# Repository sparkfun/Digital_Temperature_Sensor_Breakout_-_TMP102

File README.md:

Digital Temperature Sensor Breakout - TMP102
============================================

[*Digital Temperature Sensor Breakout - TMP102 (SEN-11931)*](https://www.sparkfun.com/products/11931)

Breakout board for TMP102 digital temperature sensor. [The datasheet can be found here.](https://www.sparkfun.com/datasheets/Sensors/Temperature/tmp102.pdf)

This board was created in Eagle v6.4.0. 

Repository Contents
-------------------

* **/Hardware** - All Eagle design files (.brd and .sch)
* **/Production** - Production panel files

Documentation
-------------------

* [Arduino Library](https://github.com/sparkfun/SparkFun_TMP102_Arduino_Library)
* [Hookup Guide](https://learn.sparkfun.com/tutorials/tmp102-digital-temperature-sensor-hookup-guide)

License Information
-------------------
The hardware is released under [Creative Commons Share-alike 3.0](http://creativecommons.org/licenses/by-sa/3.0/).  
All other code is open source so please feel free to do anything you want with it; you buy me a beer if you use this and we meet someday ([Beerware license](http://en.wikipedia.org/wiki/Beerware)).

Design by Kade Alexander Jensen

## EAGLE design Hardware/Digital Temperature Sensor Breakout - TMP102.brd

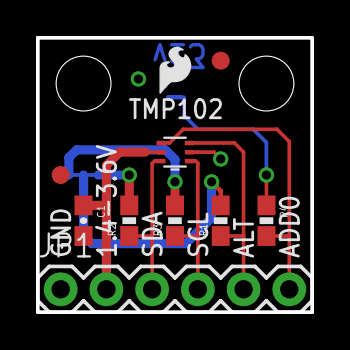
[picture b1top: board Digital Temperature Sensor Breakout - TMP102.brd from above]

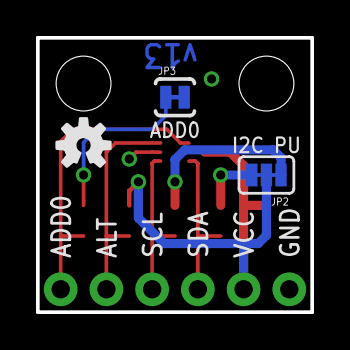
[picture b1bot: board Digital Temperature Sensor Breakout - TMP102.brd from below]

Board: 2 copper layers, 15.2 x 15.2 mm, 17 parts (3 on the bottom side), 9 nets.

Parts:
C1: 0.1uF; 0603-CAP
FRAME2: FRAME-LETTER; CREATIVE_COMMONS
JP1: 1X06
JP2: PAD-JUMPER-3-3OF3_NC_BY_TRACE_YES_SILK_FULL_BOX
JP3: ADD0; PAD-JUMPER-2-NC_BY_TRACE_YES_SILK
JP5, JP6: FIDUCIAL1X2; FIDUCIAL-1X2
JP7, JP8: STAND-OFFTIGHT; STAND-OFF-TIGHT
LOGO2: SFE_LOGO_FLAME.1_INCH; SFE_LOGO_FLAME_.1
LOGO3: OSHW-LOGOS; OSHW-LOGO-S
R1, R4: 10K; 0603-RES
R2, R3: 4.7K; 0603-RES
U1: TMP1021:1; SOT563-2
U$2: REVISION

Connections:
ADD0: JP1.6, R4.2, U1.4
ALERT: JP1.5, R1.1, U1.3
GND: C1.2, JP1.1, JP3.2, U1.2
unnamed: JP2.1, R3.2
unnamed: JP2.3, R2.2
unnamed: JP3.1, R4.1
SCL: JP1.4, R3.1, U1.1
SDA: JP1.3, R2.1, U1.6
VCC: C1.1, JP1.2, JP2.2, R1.2, U1.5

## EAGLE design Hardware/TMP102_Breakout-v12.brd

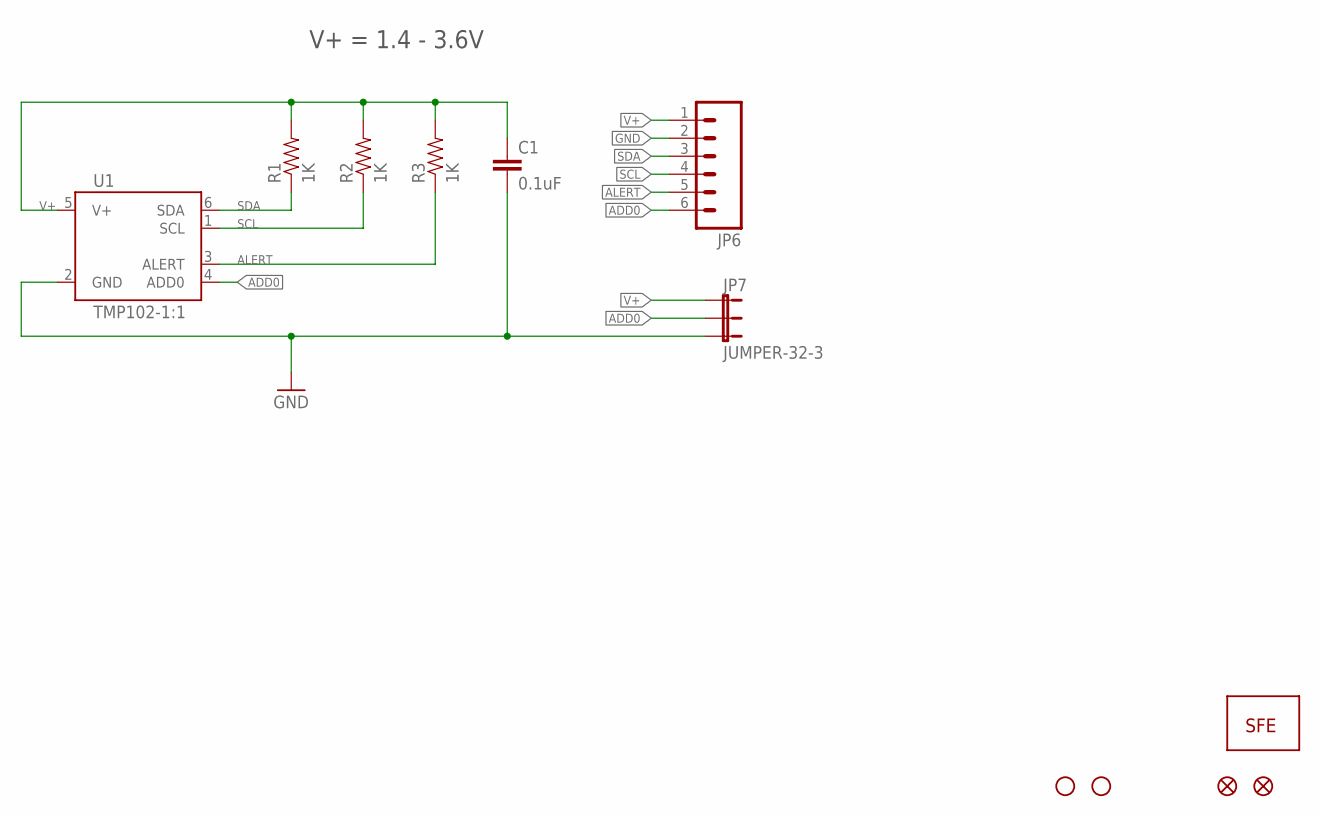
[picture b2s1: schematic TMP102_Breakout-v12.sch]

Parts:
C1: 0.1uF; 0603-CAP
JP1, JP2: STAND-OFFTIGHT; STAND-OFF-TIGHT
JP3: LOGO-SFESK; SFE-LOGO-FLAME
JP4, JP5: FIDUCIAL1X2; FIDUCIAL-1X2
JP6: M06SIP; 1X06
JP7: JUMPER-32-3; SJ_3_PASTE2&3
R1, R2, R3: 1K; 0603-RES
U1: TMP102-1:1; SOT563-2

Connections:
ADD0: JP6.6, JP7.2, U1.4 (ADD0)
ALERT: JP6.5, R3.1, U1.3 (ALERT)
GND: C1.2, JP6.2, JP7.3, U1.2 (GND)
SCL: JP6.4, R2.1, U1.1 (SCL)
SDA: JP6.3, R1.1, U1.6 (SDA)
V+: C1.1, JP6.1, JP7.1, R1.2, R2.2, R3.2, U1.5 (V+)

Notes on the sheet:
V+ = 1.4 - 3.6V

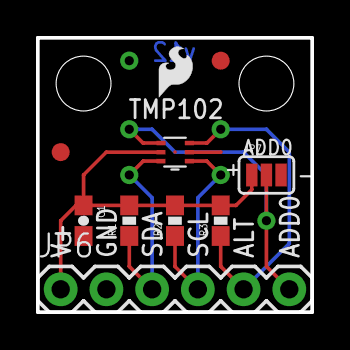
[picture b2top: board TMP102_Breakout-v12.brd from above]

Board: 2 copper layers, 15.2 x 15.2 mm, 13 parts (1 on the bottom side), 6 nets.

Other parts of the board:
U$1: OSHW-LOGO-S

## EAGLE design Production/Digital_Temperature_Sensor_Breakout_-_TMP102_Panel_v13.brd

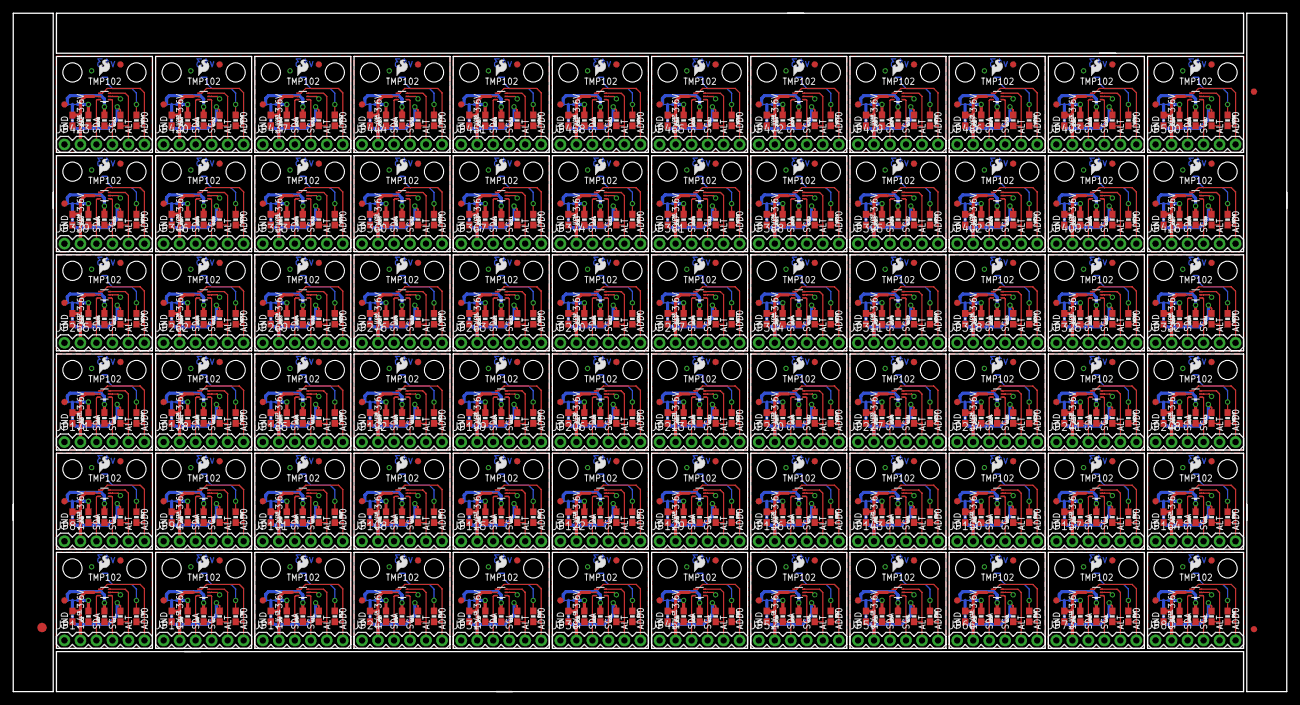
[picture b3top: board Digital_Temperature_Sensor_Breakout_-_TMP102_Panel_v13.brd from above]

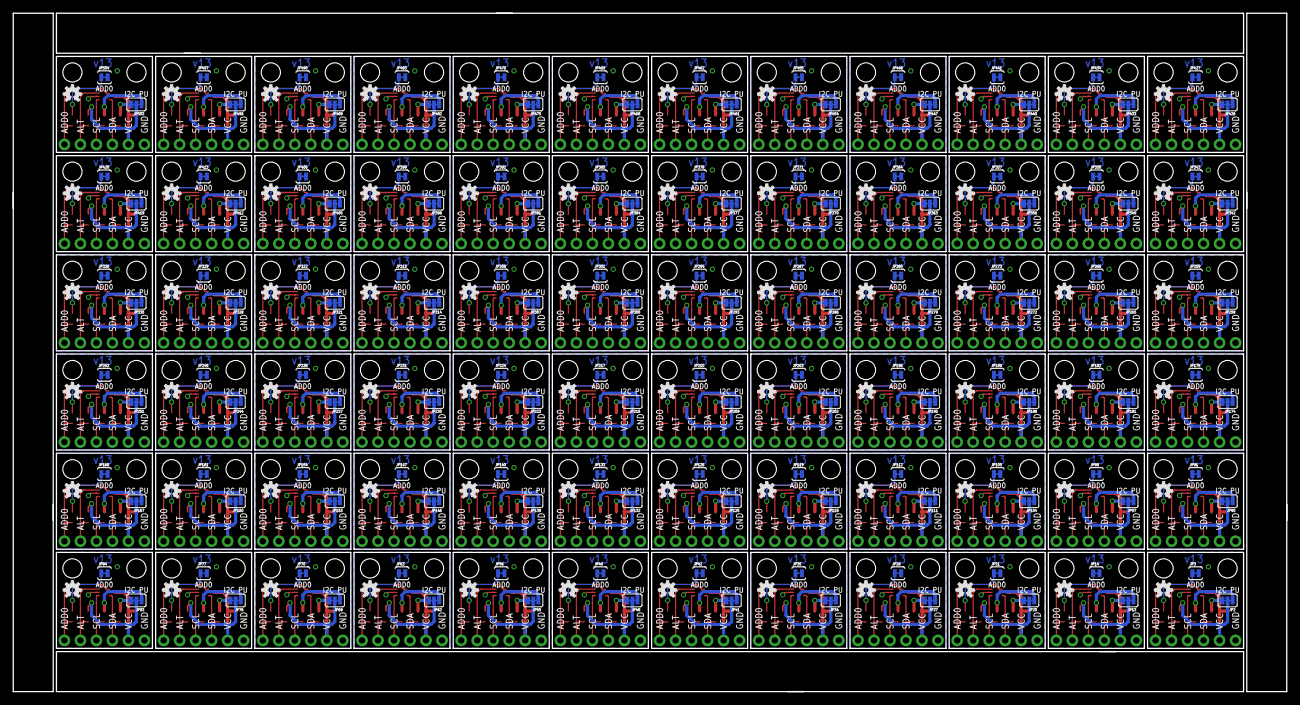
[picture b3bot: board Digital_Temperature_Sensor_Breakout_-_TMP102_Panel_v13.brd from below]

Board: 2 copper layers, 202.2 x 107.7 mm, 1083 parts (216 on the bottom side), 648 nets.

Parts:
C1, C2, C3, C4, C5, C6, C7, C8, C9, C10, C11, C12, C13, C14, C15, C16, C17, C18, C19, C20, C21, C22, C23, C24, C25, C26, C27, C28, C29, C30, C31, C32, C33, C34, C35, C36, C37, C38, C39, C40, C41, C42, C43, C44, C45, C46, C47, C48, C49, C50, C51, C52, C53, C54, C55, C56, C57, C58, C59, C60, C61, C62, C63, C64, C65, C66, C67, C68, C69, C70, C71, C72: 0.1uF; 0603-CAP
E$1: FIDUCIAL-1.5X3
E$2, E$5: FIDUCIAL-1X2
JP1, JP10, JP17, JP24, JP31, JP38, JP45, JP52, JP59, JP66, JP73, JP80, JP87, JP94, JP101, JP108, JP115, JP122, JP129, JP136, JP143, JP150, JP157, JP164, JP171, JP178, JP185, JP192, JP199, JP206, JP213, JP220, JP227, JP234, JP241, JP248, JP255, JP262, JP269, JP276, JP283, JP290, JP297, JP304, JP311, JP318, JP325, JP332, JP339, JP346, JP353, JP360, JP367, JP374, JP381, JP388, JP395, JP402, JP409, JP416, JP423, JP430, JP437, JP444, JP451, JP458, JP465, JP472, JP479, JP486, JP493, JP500: 1X06
JP2, JP13, JP20, JP27, JP34, JP41, JP48, JP55, JP62, JP69, JP76, JP83, JP90, JP97, JP104, JP111, JP118, JP125, JP132, JP139, JP146, JP153, JP160, JP167, JP174, JP181, JP188, JP195, JP202, JP209, JP216, JP223, JP230, JP237, JP244, JP251, JP258, JP265, JP272, JP279, JP286, JP293, JP300, JP307, JP314, JP321, JP328, JP335, JP342, JP349, JP356, JP363, JP370, JP377, JP384, JP391, JP398, JP405, JP412, JP419, JP426, JP433, JP440, JP447, JP454, JP461, JP468, JP475, JP482, JP489, JP496, JP503: PAD-JUMPER-3-3OF3_NC_BY_TRACE_YES_SILK_FULL_BOX
JP3, JP14, JP21, JP28, JP35, JP42, JP49, JP56, JP63, JP70, JP77, JP84, JP91, JP98, JP105, JP112, JP119, JP126, JP133, JP140, JP147, JP154, JP161, JP168, JP175, JP182, JP189, JP196, JP203, JP210, JP217, JP224, JP231, JP238, JP245, JP252, JP259, JP266, JP273, JP280, JP287, JP294, JP301, JP308, JP315, JP322, JP329, JP336, JP343, JP350, JP357, JP364, JP371, JP378, JP385, JP392, JP399, JP406, JP413, JP420, JP427, JP434, JP441, JP448, JP455, JP462, JP469, JP476, JP483, JP490, JP497, JP504: ADD0; PAD-JUMPER-2-NC_BY_TRACE_YES_SILK
JP4, JP5, JP6, JP9, JP15, JP16, JP22, JP23, JP29, JP30, JP36, JP37, JP43, JP44, JP50, JP51, JP57, JP58, JP64, JP65, JP71, JP72, JP78, JP79, JP85, JP86, JP92, JP93, JP99, JP100, JP106, JP107, JP113, JP114, JP120, JP121, JP127, JP128, JP134, JP135, JP141, JP142, JP148, JP149, JP155, JP156, JP162, JP163, JP169, JP170, JP176, JP177, JP183, JP184, JP190, JP191, JP197, JP198, JP204, JP205, JP211, JP212, JP218, JP219, JP225, JP226, JP232, JP233, JP239, JP240, JP246, JP247, JP253, JP254, JP260, JP261, JP267, JP268, JP274, JP275, JP281, JP282, JP288, JP289, JP295, JP296, JP302, JP303, JP309, JP310, JP316, JP317, JP323, JP324, JP330, JP331, JP337, JP338, JP344, JP345, JP351, JP352, JP358, JP359, JP365, JP366, JP372, JP373, JP379, JP380, JP386, JP387, JP393, JP394, JP400, JP401, JP407, JP408, JP414, JP415, JP421, JP422, JP428, JP429, JP435, JP436, JP442, JP443, JP449, JP450, JP456, JP457, JP463, JP464, JP470, JP471, JP477, JP478, JP484, JP485, JP491, JP492, JP498, JP499: FIDUCIAL1X2; FIDUCIAL-1X2
JP7, JP8, JP11, JP12, JP18, JP19, JP25, JP26, JP32, JP33, JP39, JP40, JP46, JP47, JP53, JP54, JP60, JP61, JP67, JP68, JP74, JP75, JP81, JP82, JP88, JP89, JP95, JP96, JP102, JP103, JP109, JP110, JP116, JP117, JP123, JP124, JP130, JP131, JP137, JP138, JP144, JP145, JP151, JP152, JP158, JP159, JP165, JP166, JP172, JP173, JP179, JP180, JP186, JP187, JP193, JP194, JP200, JP201, JP207, JP208, JP214, JP215, JP221, JP222, JP228, JP229, JP235, JP236, JP242, JP243, JP249, JP250, JP256, JP257, JP263, JP264, JP270, JP271, JP277, JP278, JP284, JP285, JP291, JP292, JP298, JP299, JP305, JP306, JP312, JP313, JP319, JP320, JP326, JP327, JP333, JP334, JP340, JP341, JP347, JP348, JP354, JP355, JP361, JP362, JP368, JP369, JP375, JP376, JP382, JP383, JP389, JP390, JP396, JP397, JP403, JP404, JP410, JP411, JP417, JP418, JP424, JP425, JP431, JP432, JP438, JP439, JP445, JP446, JP452, JP453, JP459, JP460, JP466, JP467, JP473, JP474, JP480, JP481, JP487, JP488, JP494, JP495, JP501, JP502: STAND-OFFTIGHT; STAND-OFF-TIGHT
LOGO1, LOGO2, LOGO5, LOGO7, LOGO9, LOGO11, LOGO13, LOGO15, LOGO17, LOGO19, LOGO21, LOGO23, LOGO25, LOGO27, LOGO29, LOGO31, LOGO33, LOGO35, LOGO37, LOGO39, LOGO41, LOGO43, LOGO45, LOGO47, LOGO49, LOGO51, LOGO53, LOGO55, LOGO57, LOGO59, LOGO61, LOGO63, LOGO65, LOGO67, LOGO69, LOGO71, LOGO73, LOGO75, LOGO77, LOGO79, LOGO81, LOGO83, LOGO85, LOGO87, LOGO89, LOGO91, LOGO93, LOGO95, LOGO97, LOGO99, LOGO101, LOGO103, LOGO105, LOGO107, LOGO109, LOGO111, LOGO113, LOGO115, LOGO117, LOGO119, LOGO121, LOGO123, LOGO125, LOGO127, LOGO129, LOGO131, LOGO133, LOGO135, LOGO137, LOGO139, LOGO141, LOGO143: SFE_LOGO_FLAME.1_INCH; SFE_LOGO_FLAME_.1
LOGO3, LOGO4, LOGO6, LOGO8, LOGO10, LOGO12, LOGO14, LOGO16, LOGO18, LOGO20, LOGO22, LOGO24, LOGO26, LOGO28, LOGO30, LOGO32, LOGO34, LOGO36, LOGO38, LOGO40, LOGO42, LOGO44, LOGO46, LOGO48, LOGO50, LOGO52, LOGO54, LOGO56, LOGO58, LOGO60, LOGO62, LOGO64, LOGO66, LOGO68, LOGO70, LOGO72, LOGO74, LOGO76, LOGO78, LOGO80, LOGO82, LOGO84, LOGO86, LOGO88, LOGO90, LOGO92, LOGO94, LOGO96, LOGO98, LOGO100, LOGO102, LOGO104, LOGO106, LOGO108, LOGO110, LOGO112, LOGO114, LOGO116, LOGO118, LOGO120, LOGO122, LOGO124, LOGO126, LOGO128, LOGO130, LOGO132, LOGO134, LOGO136, LOGO138, LOGO140, LOGO142, LOGO144: OSHW-LOGOS; OSHW-LOGO-S
R1, R4, R7, R8, R11, R12, R15, R16, R19, R20, R23, R24, R27, R28, R31, R32, R35, R36, R39, R40, R43, R44, R47, R48, R51, R52, R55, R56, R59, R60, R63, R64, R67, R68, R71, R72, R75, R76, R79, R80, R83, R84, R87, R88, R91, R92, R95, R96, R99, R100, R103, R104, R107, R108, R111, R112, R115, R116, R119, R120, R123, R124, R127, R128, R131, R132, R135, R136, R139, R140, R143, R144, R147, R148, R151, R152, R155, R156, R159, R160, R163, R164, R167, R168, R171, R172, R175, R176, R179, R180, R183, R184, R187, R188, R191, R192, R195, R196, R199, R200, R203, R204, R207, R208, R211, R212, R215, R216, R219, R220, R223, R224, R227, R228, R231, R232, R235, R236, R239, R240, R243, R244, R247, R248, R251, R252, R255, R256, R259, R260, R263, R264, R267, R268, R271, R272, R275, R276, R279, R280, R283, R284, R287, R288: 10K; 0603-RES
R2, R3, R5, R6, R9, R10, R13, R14, R17, R18, R21, R22, R25, R26, R29, R30, R33, R34, R37, R38, R41, R42, R45, R46, R49, R50, R53, R54, R57, R58, R61, R62, R65, R66, R69, R70, R73, R74, R77, R78, R81, R82, R85, R86, R89, R90, R93, R94, R97, R98, R101, R102, R105, R106, R109, R110, R113, R114, R117, R118, R121, R122, R125, R126, R129, R130, R133, R134, R137, R138, R141, R142, R145, R146, R149, R150, R153, R154, R157, R158, R161, R162, R165, R166, R169, R170, R173, R174, R177, R178, R181, R182, R185, R186, R189, R190, R193, R194, R197, R198, R201, R202, R205, R206, R209, R210, R213, R214, R217, R218, R221, R222, R225, R226, R229, R230, R233, R234, R237, R238, R241, R242, R245, R246, R249, R250, R253, R254, R257, R258, R261, R262, R265, R266, R269, R270, R273, R274, R277, R278, R281, R282, R285, R286: 4.7K; 0603-RES
U1, U2, U3, U4, U5, U6, U7, U8, U9, U10, U11, U12, U13, U14, U15, U16, U17, U18, U19, U20, U21, U22, U23, U24, U25, U26, U27, U28, U29, U30, U31, U32, U33, U34, U35, U36, U37, U38, U39, U40, U41, U42, U43, U44, U45, U46, U47, U48, U49, U50, U51, U52, U53, U54, U55, U56, U57, U58, U59, U60, U61, U62, U63, U64, U65, U66, U67, U68, U69, U70, U71, U72: TMP1021:1; SOT563-2

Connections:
ADD0: JP1.6, R4.2, U1.4
ADD1: JP10.6, R8.2, U2.4
ADD2: JP17.6, R12.2, U3.4
ADD3: JP24.6, R16.2, U4.4
ADD4: JP31.6, R20.2, U5.4
ADD5: JP38.6, R24.2, U6.4
ADD6: JP45.6, R28.2, U7.4
ADD7: JP52.6, R32.2, U8.4
ADD8: JP59.6, R36.2, U9.4
ADD9: JP66.6, R40.2, U10.4
ADD10: JP73.6, R44.2, U11.4
ADD11: JP80.6, R48.2, U12.4
ADD12: JP87.6, R52.2, U13.4
ADD13: JP94.6, R56.2, U14.4
ADD14: JP101.6, R60.2, U15.4
ADD15: JP108.6, R64.2, U16.4
ADD16: JP115.6, R68.2, U17.4
ADD17: JP122.6, R72.2, U18.4
ADD18: JP129.6, R76.2, U19.4
ADD19: JP136.6, R80.2, U20.4
ADD20: JP143.6, R84.2, U21.4
ADD21: JP150.6, R88.2, U22.4
ADD22: JP157.6, R92.2, U23.4
ADD23: JP164.6, R96.2, U24.4
ADD24: JP171.6, R100.2, U25.4
ADD25: JP178.6, R104.2, U26.4
ADD26: JP185.6, R108.2, U27.4
ADD27: JP192.6, R112.2, U28.4
ADD28: JP199.6, R116.2, U29.4
ADD29: JP206.6, R120.2, U30.4
ADD30: JP213.6, R124.2, U31.4
ADD31: JP220.6, R128.2, U32.4
ADD32: JP227.6, R132.2, U33.4
ADD33: JP234.6, R136.2, U34.4
ADD34: JP241.6, R140.2, U35.4
ADD35: JP248.6, R144.2, U36.4
ADD36: JP255.6, R148.2, U37.4
ADD37: JP262.6, R152.2, U38.4
ADD38: JP269.6, R156.2, U39.4
ADD39: JP276.6, R160.2, U40.4
ADD40: JP283.6, R164.2, U41.4
ADD41: JP290.6, R168.2, U42.4
ADD42: JP297.6, R172.2, U43.4
ADD43: JP304.6, R176.2, U44.4
ADD44: JP311.6, R180.2, U45.4
ADD45: JP318.6, R184.2, U46.4
ADD46: JP325.6, R188.2, U47.4
ADD47: JP332.6, R192.2, U48.4
ADD48: JP339.6, R196.2, U49.4
ADD49: JP346.6, R200.2, U50.4
ADD50: JP353.6, R204.2, U51.4
ADD51: JP360.6, R208.2, U52.4
ADD52: JP367.6, R212.2, U53.4
ADD53: JP374.6, R216.2, U54.4
ADD54: JP381.6, R220.2, U55.4
ADD55: JP388.6, R224.2, U56.4
ADD56: JP395.6, R228.2, U57.4
ADD57: JP402.6, R232.2, U58.4
ADD58: JP409.6, R236.2, U59.4
ADD59: JP416.6, R240.2, U60.4
ADD60: JP423.6, R244.2, U61.4
ADD61: JP430.6, R248.2, U62.4
ADD62: JP437.6, R252.2, U63.4
ADD63: JP444.6, R256.2, U64.4
ADD64: JP451.6, R260.2, U65.4
ADD65: JP458.6, R264.2, U66.4
ADD66: JP465.6, R268.2, U67.4
ADD67: JP472.6, R272.2, U68.4
ADD68: JP479.6, R276.2, U69.4
ADD69: JP486.6, R280.2, U70.4
ADD70: JP493.6, R284.2, U71.4
ADD71: JP500.6, R288.2, U72.4
ALERT: JP1.5, R1.1, U1.3
ALERT1: JP10.5, R7.1, U2.3
ALERT2: JP17.5, R11.1, U3.3
ALERT3: JP24.5, R15.1, U4.3
ALERT4: JP31.5, R19.1, U5.3
ALERT5: JP38.5, R23.1, U6.3
ALERT6: JP45.5, R27.1, U7.3
ALERT7: JP52.5, R31.1, U8.3
ALERT8: JP59.5, R35.1, U9.3
ALERT9: JP66.5, R39.1, U10.3
ALERT10: JP73.5, R43.1, U11.3
ALERT11: JP80.5, R47.1, U12.3
ALERT12: JP87.5, R51.1, U13.3
ALERT13: JP94.5, R55.1, U14.3
ALERT14: JP101.5, R59.1, U15.3
ALERT15: JP108.5, R63.1, U16.3
ALERT16: JP115.5, R67.1, U17.3
ALERT17: JP122.5, R71.1, U18.3
ALERT18: JP129.5, R75.1, U19.3
ALERT19: JP136.5, R79.1, U20.3
ALERT20: JP143.5, R83.1, U21.3
ALERT21: JP150.5, R87.1, U22.3
ALERT22: JP157.5, R91.1, U23.3
ALERT23: JP164.5, R95.1, U24.3
ALERT24: JP171.5, R99.1, U25.3
ALERT25: JP178.5, R103.1, U26.3
ALERT26: JP185.5, R107.1, U27.3
ALERT27: JP192.5, R111.1, U28.3
ALERT28: JP199.5, R115.1, U29.3
ALERT29: JP206.5, R119.1, U30.3
ALERT30: JP213.5, R123.1, U31.3
ALERT31: JP220.5, R127.1, U32.3
ALERT32: JP227.5, R131.1, U33.3
ALERT33: JP234.5, R135.1, U34.3
ALERT34: JP241.5, R139.1, U35.3
ALERT35: JP248.5, R143.1, U36.3
ALERT36: JP255.5, R147.1, U37.3
ALERT37: JP262.5, R151.1, U38.3
ALERT38: JP269.5, R155.1, U39.3
ALERT39: JP276.5, R159.1, U40.3
ALERT40: JP283.5, R163.1, U41.3
ALERT41: JP290.5, R167.1, U42.3
ALERT42: JP297.5, R171.1, U43.3
ALERT43: JP304.5, R175.1, U44.3
ALERT44: JP311.5, R179.1, U45.3
ALERT45: JP318.5, R183.1, U46.3
ALERT46: JP325.5, R187.1, U47.3
ALERT47: JP332.5, R191.1, U48.3
ALERT48: JP339.5, R195.1, U49.3
ALERT49: JP346.5, R199.1, U50.3
ALERT50: JP353.5, R203.1, U51.3
ALERT51: JP360.5, R207.1, U52.3
ALERT52: JP367.5, R211.1, U53.3
ALERT53: JP374.5, R215.1, U54.3
ALERT54: JP381.5, R219.1, U55.3
ALERT55: JP388.5, R223.1, U56.3
ALERT56: JP395.5, R227.1, U57.3
ALERT57: JP402.5, R231.1, U58.3
ALERT58: JP409.5, R235.1, U59.3
ALERT59: JP416.5, R239.1, U60.3
ALERT60: JP423.5, R243.1, U61.3
ALERT61: JP430.5, R247.1, U62.3
ALERT62: JP437.5, R251.1, U63.3
ALERT63: JP444.5, R255.1, U64.3
ALERT64: JP451.5, R259.1, U65.3
ALERT65: JP458.5, R263.1, U66.3
ALERT66: JP465.5, R267.1, U67.3
ALERT67: JP472.5, R271.1, U68.3
ALERT68: JP479.5, R275.1, U69.3
ALERT69: JP486.5, R279.1, U70.3
ALERT70: JP493.5, R283.1, U71.3
ALERT71: JP500.5, R287.1, U72.3
GND: C1.2, JP1.1, JP3.2, U1.2
GND1: C2.2, JP10.1, JP14.2, U2.2
GND2: C3.2, JP17.1, JP21.2, U3.2
GND3: C4.2, JP24.1, JP28.2, U4.2
GND4: C5.2, JP31.1, JP35.2, U5.2
GND5: C6.2, JP38.1, JP42.2, U6.2
GND6: C7.2, JP45.1, JP49.2, U7.2
GND7: C8.2, JP52.1, JP56.2, U8.2
GND8: C9.2, JP59.1, JP63.2, U9.2
GND9: C10.2, JP66.1, JP70.2, U10.2
GND10: C11.2, JP73.1, JP77.2, U11.2
GND11: C12.2, JP80.1, JP84.2, U12.2
GND12: C13.2, JP87.1, JP91.2, U13.2
GND13: C14.2, JP94.1, JP98.2, U14.2
GND14: C15.2, JP101.1, JP105.2, U15.2
GND15: C16.2, JP108.1, JP112.2, U16.2
GND16: C17.2, JP115.1, JP119.2, U17.2
GND17: C18.2, JP122.1, JP126.2, U18.2
GND18: C19.2, JP129.1, JP133.2, U19.2
GND19: C20.2, JP136.1, JP140.2, U20.2
GND20: C21.2, JP143.1, JP147.2, U21.2
GND21: C22.2, JP150.1, JP154.2, U22.2
GND22: C23.2, JP157.1, JP161.2, U23.2
GND23: C24.2, JP164.1, JP168.2, U24.2
GND24: C25.2, JP171.1, JP175.2, U25.2
GND25: C26.2, JP178.1, JP182.2, U26.2
GND26: C27.2, JP185.1, JP189.2, U27.2
GND27: C28.2, JP192.1, JP196.2, U28.2
GND28: C29.2, JP199.1, JP203.2, U29.2
GND29: C30.2, JP206.1, JP210.2, U30.2
GND30: C31.2, JP213.1, JP217.2, U31.2
GND31: C32.2, JP220.1, JP224.2, U32.2
GND32: C33.2, JP227.1, JP231.2, U33.2
GND33: C34.2, JP234.1, JP238.2, U34.2
GND34: C35.2, JP241.1, JP245.2, U35.2
GND35: C36.2, JP248.1, JP252.2, U36.2
GND36: C37.2, JP255.1, JP259.2, U37.2
GND37: C38.2, JP262.1, JP266.2, U38.2
GND38: C39.2, JP269.1, JP273.2, U39.2
GND39: C40.2, JP276.1, JP280.2, U40.2
GND40: C41.2, JP283.1, JP287.2, U41.2
GND41: C42.2, JP290.1, JP294.2, U42.2
GND42: C43.2, JP297.1, JP301.2, U43.2
GND43: C44.2, JP304.1, JP308.2, U44.2
GND44: C45.2, JP311.1, JP315.2, U45.2
GND45: C46.2, JP318.1, JP322.2, U46.2
GND46: C47.2, JP325.1, JP329.2, U47.2
GND47: C48.2, JP332.1, JP336.2, U48.2
GND48: C49.2, JP339.1, JP343.2, U49.2
GND49: C50.2, JP346.1, JP350.2, U50.2
GND50: C51.2, JP353.1, JP357.2, U51.2
GND51: C52.2, JP360.1, JP364.2, U52.2
GND52: C53.2, JP367.1, JP371.2, U53.2
GND53: C54.2, JP374.1, JP378.2, U54.2
GND54: C55.2, JP381.1, JP385.2, U55.2
GND55: C56.2, JP388.1, JP392.2, U56.2
GND56: C57.2, JP395.1, JP399.2, U57.2
GND57: C58.2, JP402.1, JP406.2, U58.2
GND58: C59.2, JP409.1, JP413.2, U59.2
GND59: C60.2, JP416.1, JP420.2, U60.2
GND60: C61.2, JP423.1, JP427.2, U61.2
GND61: C62.2, JP430.1, JP434.2, U62.2
GND62: C63.2, JP437.1, JP441.2, U63.2
GND63: C64.2, JP444.1, JP448.2, U64.2
GND64: C65.2, JP451.1, JP455.2, U65.2
GND65: C66.2, JP458.1, JP462.2, U66.2
GND66: C67.2, JP465.1, JP469.2, U67.2
GND67: C68.2, JP472.1, JP476.2, U68.2
GND68: C69.2, JP479.1, JP483.2, U69.2
GND69: C70.2, JP486.1, JP490.2, U70.2
GND70: C71.2, JP493.1, JP497.2, U71.2
GND71: C72.2, JP500.1, JP504.2, U72.2
unnamed: JP2.1, R3.2
unnamed: JP2.3, R2.2
unnamed: JP3.1, R4.1
unnamed: JP13.1, R6.2
unnamed: JP13.3, R5.2
unnamed: JP14.1, R8.1
unnamed: JP20.1, R10.2
unnamed: JP20.3, R9.2
unnamed: JP21.1, R12.1
unnamed: JP27.1, R14.2
unnamed: JP27.3, R13.2
unnamed: JP28.1, R16.1
unnamed: JP34.1, R18.2
unnamed: JP34.3, R17.2
unnamed: JP35.1, R20.1
unnamed: JP41.1, R22.2
unnamed: JP41.3, R21.2
unnamed: JP42.1, R24.1
unnamed: JP48.1, R26.2
unnamed: JP48.3, R25.2
unnamed: JP49.1, R28.1
unnamed: JP55.1, R30.2
unnamed: JP55.3, R29.2
unnamed: JP56.1, R32.1
unnamed: JP62.1, R34.2
unnamed: JP62.3, R33.2
unnamed: JP63.1, R36.1
unnamed: JP69.1, R38.2
unnamed: JP69.3, R37.2
unnamed: JP70.1, R40.1
unnamed: JP76.1, R42.2
unnamed: JP76.3, R41.2
unnamed: JP77.1, R44.1
unnamed: JP83.1, R46.2
unnamed: JP83.3, R45.2
unnamed: JP84.1, R48.1
unnamed: JP90.1, R50.2
unnamed: JP90.3, R49.2
unnamed: JP91.1, R52.1
unnamed: JP97.1, R54.2
unnamed: JP97.3, R53.2
unnamed: JP98.1, R56.1
unnamed: JP104.1, R58.2
unnamed: JP104.3, R57.2
unnamed: JP105.1, R60.1
unnamed: JP111.1, R62.2
unnamed: JP111.3, R61.2
unnamed: JP112.1, R64.1
unnamed: JP118.1, R66.2
unnamed: JP118.3, R65.2
unnamed: JP119.1, R68.1
unnamed: JP125.1, R70.2
unnamed: JP125.3, R69.2
unnamed: JP126.1, R72.1
unnamed: JP132.1, R74.2
unnamed: JP132.3, R73.2
unnamed: JP133.1, R76.1
unnamed: JP139.1, R78.2
unnamed: JP139.3, R77.2
unnamed: JP140.1, R80.1
unnamed: JP146.1, R82.2
unnamed: JP146.3, R81.2
unnamed: JP147.1, R84.1
unnamed: JP153.1, R86.2
unnamed: JP153.3, R85.2
unnamed: JP154.1, R88.1
unnamed: JP160.1, R90.2
unnamed: JP160.3, R89.2
unnamed: JP161.1, R92.1
unnamed: JP167.1, R94.2
unnamed: JP167.3, R93.2
unnamed: JP168.1, R96.1
unnamed: JP174.1, R98.2
unnamed: JP174.3, R97.2
unnamed: JP175.1, R100.1
unnamed: JP181.1, R102.2
unnamed: JP181.3, R101.2
unnamed: JP182.1, R104.1
unnamed: JP188.1, R106.2
unnamed: JP188.3, R105.2
unnamed: JP189.1, R108.1
unnamed: JP195.1, R110.2
unnamed: JP195.3, R109.2
unnamed: JP196.1, R112.1
unnamed: JP202.1, R114.2
unnamed: JP202.3, R113.2
unnamed: JP203.1, R116.1
unnamed: JP209.1, R118.2
unnamed: JP209.3, R117.2
unnamed: JP210.1, R120.1
unnamed: JP216.1, R122.2
unnamed: JP216.3, R121.2
unnamed: JP217.1, R124.1
unnamed: JP223.1, R126.2
unnamed: JP223.3, R125.2
unnamed: JP224.1, R128.1
unnamed: JP230.1, R130.2
unnamed: JP230.3, R129.2
unnamed: JP231.1, R132.1
unnamed: JP237.1, R134.2
unnamed: JP237.3, R133.2
unnamed: JP238.1, R136.1
unnamed: JP244.1, R138.2
unnamed: JP244.3, R137.2
unnamed: JP245.1, R140.1
unnamed: JP251.1, R142.2
unnamed: JP251.3, R141.2
unnamed: JP252.1, R144.1
unnamed: JP258.1, R146.2
unnamed: JP258.3, R145.2
unnamed: JP259.1, R148.1
unnamed: JP265.1, R150.2
unnamed: JP265.3, R149.2
unnamed: JP266.1, R152.1
unnamed: JP272.1, R154.2
unnamed: JP272.3, R153.2
unnamed: JP273.1, R156.1
unnamed: JP279.1, R158.2
unnamed: JP279.3, R157.2
unnamed: JP280.1, R160.1
unnamed: JP286.1, R162.2
unnamed: JP286.3, R161.2
unnamed: JP287.1, R164.1
unnamed: JP293.1, R166.2
unnamed: JP293.3, R165.2
unnamed: JP294.1, R168.1
unnamed: JP300.1, R170.2
unnamed: JP300.3, R169.2
unnamed: JP301.1, R172.1
unnamed: JP307.1, R174.2
unnamed: JP307.3, R173.2
unnamed: JP308.1, R176.1
unnamed: JP314.1, R178.2
unnamed: JP314.3, R177.2
unnamed: JP315.1, R180.1
unnamed: JP321.1, R182.2
unnamed: JP321.3, R181.2
unnamed: JP322.1, R184.1
unnamed: JP328.1, R186.2
unnamed: JP328.3, R185.2
unnamed: JP329.1, R188.1
unnamed: JP335.1, R190.2
unnamed: JP335.3, R189.2
unnamed: JP336.1, R192.1
unnamed: JP342.1, R194.2
unnamed: JP342.3, R193.2
unnamed: JP343.1, R196.1
unnamed: JP349.1, R198.2
unnamed: JP349.3, R197.2
unnamed: JP350.1, R200.1
unnamed: JP356.1, R202.2
unnamed: JP356.3, R201.2
unnamed: JP357.1, R204.1
unnamed: JP363.1, R206.2
unnamed: JP363.3, R205.2
unnamed: JP364.1, R208.1
unnamed: JP370.1, R210.2
unnamed: JP370.3, R209.2
unnamed: JP371.1, R212.1
unnamed: JP377.1, R214.2
unnamed: JP377.3, R213.2
unnamed: JP378.1, R216.1
unnamed: JP384.1, R218.2
unnamed: JP384.3, R217.2
unnamed: JP385.1, R220.1
unnamed: JP391.1, R222.2
unnamed: JP391.3, R221.2
unnamed: JP392.1, R224.1
unnamed: JP398.1, R226.2
unnamed: JP398.3, R225.2
unnamed: JP399.1, R228.1
unnamed: JP405.1, R230.2
unnamed: JP405.3, R229.2
unnamed: JP406.1, R232.1
unnamed: JP412.1, R234.2
unnamed: JP412.3, R233.2
unnamed: JP413.1, R236.1
unnamed: JP419.1, R238.2
unnamed: JP419.3, R237.2
unnamed: JP420.1, R240.1
unnamed: JP426.1, R242.2
unnamed: JP426.3, R241.2
unnamed: JP427.1, R244.1
unnamed: JP433.1, R246.2
unnamed: JP433.3, R245.2
unnamed: JP434.1, R248.1
unnamed: JP440.1, R250.2
unnamed: JP440.3, R249.2
unnamed: JP441.1, R252.1
unnamed: JP447.1, R254.2
unnamed: JP447.3, R253.2
unnamed: JP448.1, R256.1
unnamed: JP454.1, R258.2
unnamed: JP454.3, R257.2
unnamed: JP455.1, R260.1
unnamed: JP461.1, R262.2
unnamed: JP461.3, R261.2
unnamed: JP462.1, R264.1
unnamed: JP468.1, R266.2
unnamed: JP468.3, R265.2
unnamed: JP469.1, R268.1
unnamed: JP475.1, R270.2
unnamed: JP475.3, R269.2
unnamed: JP476.1, R272.1
unnamed: JP482.1, R274.2
unnamed: JP482.3, R273.2
unnamed: JP483.1, R276.1
unnamed: JP489.1, R278.2
unnamed: JP489.3, R277.2
unnamed: JP490.1, R280.1
unnamed: JP496.1, R282.2
unnamed: JP496.3, R281.2
unnamed: JP497.1, R284.1
unnamed: JP503.1, R286.2
unnamed: JP503.3, R285.2
unnamed: JP504.1, R288.1
SCL: JP1.4, R3.1, U1.1
SCL1: JP10.4, R6.1, U2.1
SCL2: JP17.4, R10.1, U3.1
SCL3: JP24.4, R14.1, U4.1
SCL4: JP31.4, R18.1, U5.1
SCL5: JP38.4, R22.1, U6.1
SCL6: JP45.4, R26.1, U7.1
SCL7: JP52.4, R30.1, U8.1
SCL8: JP59.4, R34.1, U9.1
SCL9: JP66.4, R38.1, U10.1
SCL10: JP73.4, R42.1, U11.1
SCL11: JP80.4, R46.1, U12.1
SCL12: JP87.4, R50.1, U13.1
SCL13: JP94.4, R54.1, U14.1
SCL14: JP101.4, R58.1, U15.1
SCL15: JP108.4, R62.1, U16.1
SCL16: JP115.4, R66.1, U17.1
SCL17: JP122.4, R70.1, U18.1
SCL18: JP129.4, R74.1, U19.1
SCL19: JP136.4, R78.1, U20.1
SCL20: JP143.4, R82.1, U21.1
SCL21: JP150.4, R86.1, U22.1
SCL22: JP157.4, R90.1, U23.1
SCL23: JP164.4, R94.1, U24.1
SCL24: JP171.4, R98.1, U25.1
SCL25: JP178.4, R102.1, U26.1
SCL26: JP185.4, R106.1, U27.1
SCL27: JP192.4, R110.1, U28.1
SCL28: JP199.4, R114.1, U29.1
SCL29: JP206.4, R118.1, U30.1
SCL30: JP213.4, R122.1, U31.1
SCL31: JP220.4, R126.1, U32.1
SCL32: JP227.4, R130.1, U33.1
SCL33: JP234.4, R134.1, U34.1
SCL34: JP241.4, R138.1, U35.1
SCL35: JP248.4, R142.1, U36.1
SCL36: JP255.4, R146.1, U37.1
SCL37: JP262.4, R150.1, U38.1
SCL38: JP269.4, R154.1, U39.1
SCL39: JP276.4, R158.1, U40.1
SCL40: JP283.4, R162.1, U41.1
SCL41: JP290.4, R166.1, U42.1
SCL42: JP297.4, R170.1, U43.1
SCL43: JP304.4, R174.1, U44.1
SCL44: JP311.4, R178.1, U45.1
SCL45: JP318.4, R182.1, U46.1
SCL46: JP325.4, R186.1, U47.1
SCL47: JP332.4, R190.1, U48.1
SCL48: JP339.4, R194.1, U49.1
SCL49: JP346.4, R198.1, U50.1
SCL50: JP353.4, R202.1, U51.1
SCL51: JP360.4, R206.1, U52.1
SCL52: JP367.4, R210.1, U53.1
SCL53: JP374.4, R214.1, U54.1
SCL54: JP381.4, R218.1, U55.1
SCL55: JP388.4, R222.1, U56.1
SCL56: JP395.4, R226.1, U57.1
SCL57: JP402.4, R230.1, U58.1
SCL58: JP409.4, R234.1, U59.1
SCL59: JP416.4, R238.1, U60.1
SCL60: JP423.4, R242.1, U61.1
SCL61: JP430.4, R246.1, U62.1
SCL62: JP437.4, R250.1, U63.1
SCL63: JP444.4, R254.1, U64.1
SCL64: JP451.4, R258.1, U65.1
SCL65: JP458.4, R262.1, U66.1
SCL66: JP465.4, R266.1, U67.1
SCL67: JP472.4, R270.1, U68.1
SCL68: JP479.4, R274.1, U69.1
SCL69: JP486.4, R278.1, U70.1
SCL70: JP493.4, R282.1, U71.1
SCL71: JP500.4, R286.1, U72.1
SDA: JP1.3, R2.1, U1.6
SDA1: JP10.3, R5.1, U2.6
SDA2: JP17.3, R9.1, U3.6
SDA3: JP24.3, R13.1, U4.6
SDA4: JP31.3, R17.1, U5.6
SDA5: JP38.3, R21.1, U6.6
SDA6: JP45.3, R25.1, U7.6
SDA7: JP52.3, R29.1, U8.6
SDA8: JP59.3, R33.1, U9.6
SDA9: JP66.3, R37.1, U10.6
SDA10: JP73.3, R41.1, U11.6
SDA11: JP80.3, R45.1, U12.6
SDA12: JP87.3, R49.1, U13.6
SDA13: JP94.3, R53.1, U14.6
SDA14: JP101.3, R57.1, U15.6
SDA15: JP108.3, R61.1, U16.6
SDA16: JP115.3, R65.1, U17.6
SDA17: JP122.3, R69.1, U18.6
SDA18: JP129.3, R73.1, U19.6
SDA19: JP136.3, R77.1, U20.6
SDA20: JP143.3, R81.1, U21.6
SDA21: JP150.3, R85.1, U22.6
SDA22: JP157.3, R89.1, U23.6
SDA23: JP164.3, R93.1, U24.6
SDA24: JP171.3, R97.1, U25.6
SDA25: JP178.3, R101.1, U26.6
SDA26: JP185.3, R105.1, U27.6
SDA27: JP192.3, R109.1, U28.6
SDA28: JP199.3, R113.1, U29.6
SDA29: JP206.3, R117.1, U30.6
SDA30: JP213.3, R121.1, U31.6
SDA31: JP220.3, R125.1, U32.6
SDA32: JP227.3, R129.1, U33.6
SDA33: JP234.3, R133.1, U34.6
SDA34: JP241.3, R137.1, U35.6
SDA35: JP248.3, R141.1, U36.6
SDA36: JP255.3, R145.1, U37.6
SDA37: JP262.3, R149.1, U38.6
SDA38: JP269.3, R153.1, U39.6
SDA39: JP276.3, R157.1, U40.6
SDA40: JP283.3, R161.1, U41.6
SDA41: JP290.3, R165.1, U42.6
SDA42: JP297.3, R169.1, U43.6
SDA43: JP304.3, R173.1, U44.6
SDA44: JP311.3, R177.1, U45.6
SDA45: JP318.3, R181.1, U46.6
SDA46: JP325.3, R185.1, U47.6
SDA47: JP332.3, R189.1, U48.6
SDA48: JP339.3, R193.1, U49.6
SDA49: JP346.3, R197.1, U50.6
SDA50: JP353.3, R201.1, U51.6
SDA51: JP360.3, R205.1, U52.6
SDA52: JP367.3, R209.1, U53.6
SDA53: JP374.3, R213.1, U54.6
SDA54: JP381.3, R217.1, U55.6
SDA55: JP388.3, R221.1, U56.6
SDA56: JP395.3, R225.1, U57.6
SDA57: JP402.3, R229.1, U58.6
SDA58: JP409.3, R233.1, U59.6
SDA59: JP416.3, R237.1, U60.6
SDA60: JP423.3, R241.1, U61.6
SDA61: JP430.3, R245.1, U62.6
SDA62: JP437.3, R249.1, U63.6
SDA63: JP444.3, R253.1, U64.6
SDA64: JP451.3, R257.1, U65.6
SDA65: JP458.3, R261.1, U66.6
SDA66: JP465.3, R265.1, U67.6
SDA67: JP472.3, R269.1, U68.6
SDA68: JP479.3, R273.1, U69.6
SDA69: JP486.3, R277.1, U70.6
SDA70: JP493.3, R281.1, U71.6
SDA71: JP500.3, R285.1, U72.6
VCC: C1.1, JP1.2, JP2.2, R1.2, U1.5
VCC1: C2.1, JP10.2, JP13.2, R7.2, U2.5
VCC2: C3.1, JP17.2, JP20.2, R11.2, U3.5
VCC3: C4.1, JP24.2, JP27.2, R15.2, U4.5
VCC4: C5.1, JP31.2, JP34.2, R19.2, U5.5
VCC5: C6.1, JP38.2, JP41.2, R23.2, U6.5
VCC6: C7.1, JP45.2, JP48.2, R27.2, U7.5
VCC7: C8.1, JP52.2, JP55.2, R31.2, U8.5
VCC8: C9.1, JP59.2, JP62.2, R35.2, U9.5
VCC9: C10.1, JP66.2, JP69.2, R39.2, U10.5
VCC10: C11.1, JP73.2, JP76.2, R43.2, U11.5
VCC11: C12.1, JP80.2, JP83.2, R47.2, U12.5
VCC12: C13.1, JP87.2, JP90.2, R51.2, U13.5
VCC13: C14.1, JP94.2, JP97.2, R55.2, U14.5
VCC14: C15.1, JP101.2, JP104.2, R59.2, U15.5
VCC15: C16.1, JP108.2, JP111.2, R63.2, U16.5
VCC16: C17.1, JP115.2, JP118.2, R67.2, U17.5
VCC17: C18.1, JP122.2, JP125.2, R71.2, U18.5
VCC18: C19.1, JP129.2, JP132.2, R75.2, U19.5
VCC19: C20.1, JP136.2, JP139.2, R79.2, U20.5
VCC20: C21.1, JP143.2, JP146.2, R83.2, U21.5
VCC21: C22.1, JP150.2, JP153.2, R87.2, U22.5
VCC22: C23.1, JP157.2, JP160.2, R91.2, U23.5
VCC23: C24.1, JP164.2, JP167.2, R95.2, U24.5
VCC24: C25.1, JP171.2, JP174.2, R99.2, U25.5
VCC25: C26.1, JP178.2, JP181.2, R103.2, U26.5
VCC26: C27.1, JP185.2, JP188.2, R107.2, U27.5
VCC27: C28.1, JP192.2, JP195.2, R111.2, U28.5
VCC28: C29.1, JP199.2, JP202.2, R115.2, U29.5
VCC29: C30.1, JP206.2, JP209.2, R119.2, U30.5
VCC30: C31.1, JP213.2, JP216.2, R123.2, U31.5
VCC31: C32.1, JP220.2, JP223.2, R127.2, U32.5
VCC32: C33.1, JP227.2, JP230.2, R131.2, U33.5
VCC33: C34.1, JP234.2, JP237.2, R135.2, U34.5
VCC34: C35.1, JP241.2, JP244.2, R139.2, U35.5
VCC35: C36.1, JP248.2, JP251.2, R143.2, U36.5
VCC36: C37.1, JP255.2, JP258.2, R147.2, U37.5
VCC37: C38.1, JP262.2, JP265.2, R151.2, U38.5
VCC38: C39.1, JP269.2, JP272.2, R155.2, U39.5
VCC39: C40.1, JP276.2, JP279.2, R159.2, U40.5
VCC40: C41.1, JP283.2, JP286.2, R163.2, U41.5
VCC41: C42.1, JP290.2, JP293.2, R167.2, U42.5
VCC42: C43.1, JP297.2, JP300.2, R171.2, U43.5
VCC43: C44.1, JP304.2, JP307.2, R175.2, U44.5
VCC44: C45.1, JP311.2, JP314.2, R179.2, U45.5
VCC45: C46.1, JP318.2, JP321.2, R183.2, U46.5
VCC46: C47.1, JP325.2, JP328.2, R187.2, U47.5
VCC47: C48.1, JP332.2, JP335.2, R191.2, U48.5
VCC48: C49.1, JP339.2, JP342.2, R195.2, U49.5
VCC49: C50.1, JP346.2, JP349.2, R199.2, U50.5
VCC50: C51.1, JP353.2, JP356.2, R203.2, U51.5
VCC51: C52.1, JP360.2, JP363.2, R207.2, U52.5
VCC52: C53.1, JP367.2, JP370.2, R211.2, U53.5
VCC53: C54.1, JP374.2, JP377.2, R215.2, U54.5
VCC54: C55.1, JP381.2, JP384.2, R219.2, U55.5
VCC55: C56.1, JP388.2, JP391.2, R223.2, U56.5
VCC56: C57.1, JP395.2, JP398.2, R227.2, U57.5
VCC57: C58.1, JP402.2, JP405.2, R231.2, U58.5
VCC58: C59.1, JP409.2, JP412.2, R235.2, U59.5
VCC59: C60.1, JP416.2, JP419.2, R239.2, U60.5
VCC60: C61.1, JP423.2, JP426.2, R243.2, U61.5
VCC61: C62.1, JP430.2, JP433.2, R247.2, U62.5
VCC62: C63.1, JP437.2, JP440.2, R251.2, U63.5
VCC63: C64.1, JP444.2, JP447.2, R255.2, U64.5
VCC64: C65.1, JP451.2, JP454.2, R259.2, U65.5
VCC65: C66.1, JP458.2, JP461.2, R263.2, U66.5
VCC66: C67.1, JP465.2, JP468.2, R267.2, U67.5
VCC67: C68.1, JP472.2, JP475.2, R271.2, U68.5
VCC68: C69.1, JP479.2, JP482.2, R275.2, U69.5
VCC69: C70.1, JP486.2, JP489.2, R279.2, U70.5
VCC70: C71.1, JP493.2, JP496.2, R283.2, U71.5
VCC71: C72.1, JP500.2, JP503.2, R287.2, U72.5

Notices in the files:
parts and their libraries:
SparkFun-Sensors: Licensing: CC v3.0 Share-Alike You are welcome to use this library for commercial purposes.
SparkFun-Aesthetics: Released under the Creative Commons Attribution Share-Alike 4.0 License
SparkFun-Aesthetics: https://creativecommons.org/licenses/by-sa/4.0
